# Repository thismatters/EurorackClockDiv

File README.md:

# Clock Divider (Binary)

This module reduces a clock signal by powers of two.

This is a hobbling together of elements featuring a three-layer stackup with a front face, a layer for all the jacks, and a power/processing layer where all the SMD components are layed out.

The input clock signal is passed through a schmitt trigger which is lifted whole-cloth from the [Yusynth Clock divider](https://yusynth.net/Modular/EN/DIVIDER/index.html) from which the reset signal processing is also lifted.
This module's function is distinct from the aforementioned Yusynth module in that it subdivides the clock by halves. The remainder of the circuit is a bog standard usage of the CD4040.

As with other modules in this line, this clock divider features:
* Polarity protection so that a backward power header doesn't fry anything (twin series schotty diodes: BAT54SL),
* Full surface mount design.

The KiCAD project here uses the library/footprints [found in my companion repo](https://github.com/thismatters/EurorackKiCAD).

## Width

11hp on an [Intellijel 1U rack](https://intellijel.com/support/1u-technical-specifications/).

## Inputs

Jacks:
* Input
* Reset

## Outputs

There are 6 output jacks each outputting a clock signal reduced by the labeled fraction.

## Adjustment

No adjustment required.

## Vendors

There are part numbers in the [BOM](clkdiv.csv) for many of the parts (not for basic passives though) at the following vendors:

* [Mouser](https://www.mouser.com): Needs no introduction. Get your ICs from here (or [digikey](https://www.digikey.com)).
* [Tayda Electronics](https://www.taydaelectronics.com/): Good supplier for passive components; audio jacks, and potentiometers. Their audio jacks are slightly smaller than the thonkiconn from thonk.
* [Love My Switches](https://lovemyswitches.com/): Has [really good knobs](https://lovemyswitches.com/anodized-aluminum-knob-the-lo-fi-1-4-smooth-shaft-12-5mm-od/) to go on those potentiometers!
* [OSHPark](https://oshpark.com/): Fast and (relatively) cheap PCB manufacturer. [V0 PCB](https://oshpark.com/shared_projects/ADWTtPJV)

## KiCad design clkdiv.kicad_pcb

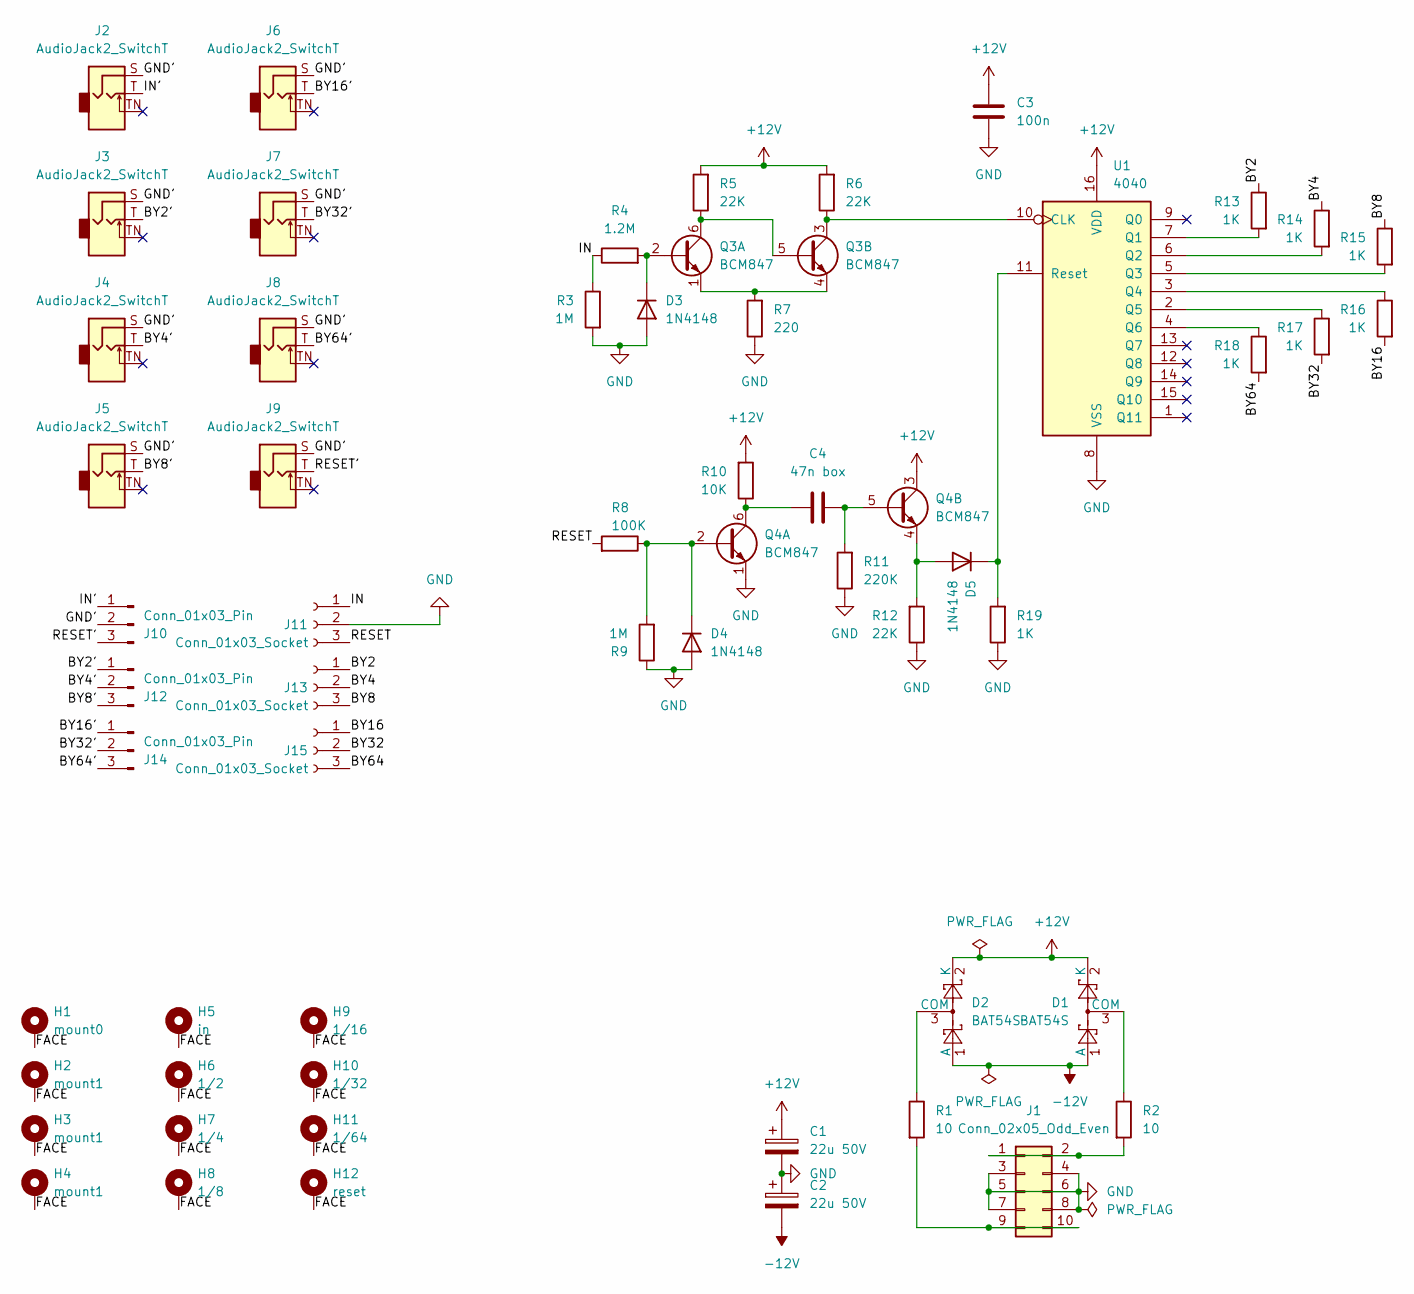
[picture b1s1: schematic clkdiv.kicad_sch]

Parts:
C1, C2: 22u 50V; CP_Radial_D5.0mm_P2.50mm
C3: 100n; C_0805_2012Metric
C4: 47n box; C_Rect_L7.2mm_W2.5mm_P5.00mm_FKS2_FKP2_MKS2_MKP2
D1, D2: BAT54S; SOT-23; PartNum 863-BAT54SLT1G
D3, D4, D5: 1N4148; D_SOD-323_HandSoldering
H1: mount0; Mech-MountingHole
H2, H3, H4: mount1; Mech-MountingHole
H5: in; Mech-AudioJack-Hole-Input-Clock
H6: 1/2; Mech-AudioJack-Hole-Output-Clock
H7: 1/4; Mech-AudioJack-Hole-Output-Clock
H8: 1/8; Mech-AudioJack-Hole-Output-Clock
H9: 1/16; Mech-AudioJack-Hole-Output-Clock
H10: 1/32; Mech-AudioJack-Hole-Output-Clock
H11: 1/64; Mech-AudioJack-Hole-Output-Clock
H12: reset; Mech-AudioJack-Hole-Input-Gate
J1: Conn_02x05_Odd_Even; PinHeader_2x05_P2.54mm_Vertical; PartNum A-2939
J2, J3, J4, J5, J6, J7, J8, J9: AudioJack2_SwitchT; AudioJack2_Tayda_A-2566; PartNum A-2566
J10, J12, J14: Conn_01x03_Pin; PinHeader_1x03_P2.54mm_Vertical
J11, J13, J15: Conn_01x03_Socket; PinSocket_1x03_P2.54mm_Vertical
Q3, Q4: BCM847; TSOP-6_1.65x3.05mm_P0.95mm; PartNum 771-BCM847DS135
R1, R2: 10; R_0805_2012Metric
R3, R9: 1M; R_0805_2012Metric
R4: 1.2M; R_0805_2012Metric
R5, R6, R12: 22K; R_0805_2012Metric
R7: 220; R_0805_2012Metric
R8: 100K; R_0805_2012Metric
R10: 10K; R_0805_2012Metric
R11: 220K; R_0805_2012Metric
R13, R14, R15, R16, R17, R18, R19: 1K; R_0805_2012Metric
U1: 4040; TSSOP-16_4.4x5mm_P0.65mm; PartNum 595-CD4040BPWR

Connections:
+12V: C1.1, C3.1, D1.2 (K), D2.2 (K), Q4.3 (C2), R5.2, R6.2, R10.2, U1.16 (VDD)
-12V: C2.2, D1.1 (A), D2.1 (A)
/BY2: J13.1, R13.1
/BY2': J3.T, J12.1
/BY4: J13.2, R14.1
/BY4': J4.T, J12.2
/BY8: J13.3, R15.1
/BY8': J5.T, J12.3
/BY16: J15.1, R16.2
/BY16': J6.T, J14.1
/BY32: J15.2, R17.2
/BY32': J7.T, J14.2
/BY64: J15.3, R18.2
/BY64': J8.T, J14.3
/FACE: H1.1, H2.1, H3.1, H4.1, H5.1, H6.1, H7.1, H8.1, H9.1, H10.1, H11.1, H12.1
/GND': J2.S, J3.S, J4.S, J5.S, J6.S, J7.S, J8.S, J9.S, J10.2
/IN: J11.1, R3.1, R4.1
/IN': J2.T, J10.1
/RESET: J11.3, R8.2
/RESET': J9.T, J10.3
GND: C1.2, C2.1, C3.2, D3.2 (A), D4.2 (A), J1.3, J1.4, J1.5, J1.6, J1.7, J1.8, J11.2, Q4.1 (E1), R3.2, R7.1, R9.1, R11.1, R12.1, R19.1, U1.8 (VSS)
unnamed: D1.3 (COM), R2.1
unnamed: D2.3 (COM), R1.1
unnamed: D3.1 (K), Q3.2 (B1), R4.2
unnamed: D4.1 (K), Q4.2 (B1), R8.1, R9.2
unnamed: D5.2 (A), Q4.4 (E2), R12.2
unnamed: D5.1 (K), R19.2, U1.11 (Reset)
unnamed: J1.1, J1.2, R2.2
unnamed: J1.9, J1.10, R1.2
unnamed: Q3.5 (B2), Q3.6 (C1), R5.1
unnamed: Q3.1 (E1), Q3.4 (E2), R7.2
unnamed: Q3.3 (C2), R6.1, U1.10 (CLK)
unnamed: C4.1, Q4.6 (C1), R10.1
unnamed: C4.2, Q4.5 (B2), R11.2
unnamed: R13.2, U1.7 (Q1)
unnamed: R14.2, U1.6 (Q2)
unnamed: R15.2, U1.5 (Q3)
unnamed: R16.1, U1.3 (Q4)
unnamed: R17.1, U1.2 (Q5)
unnamed: R18.1, U1.4 (Q6)

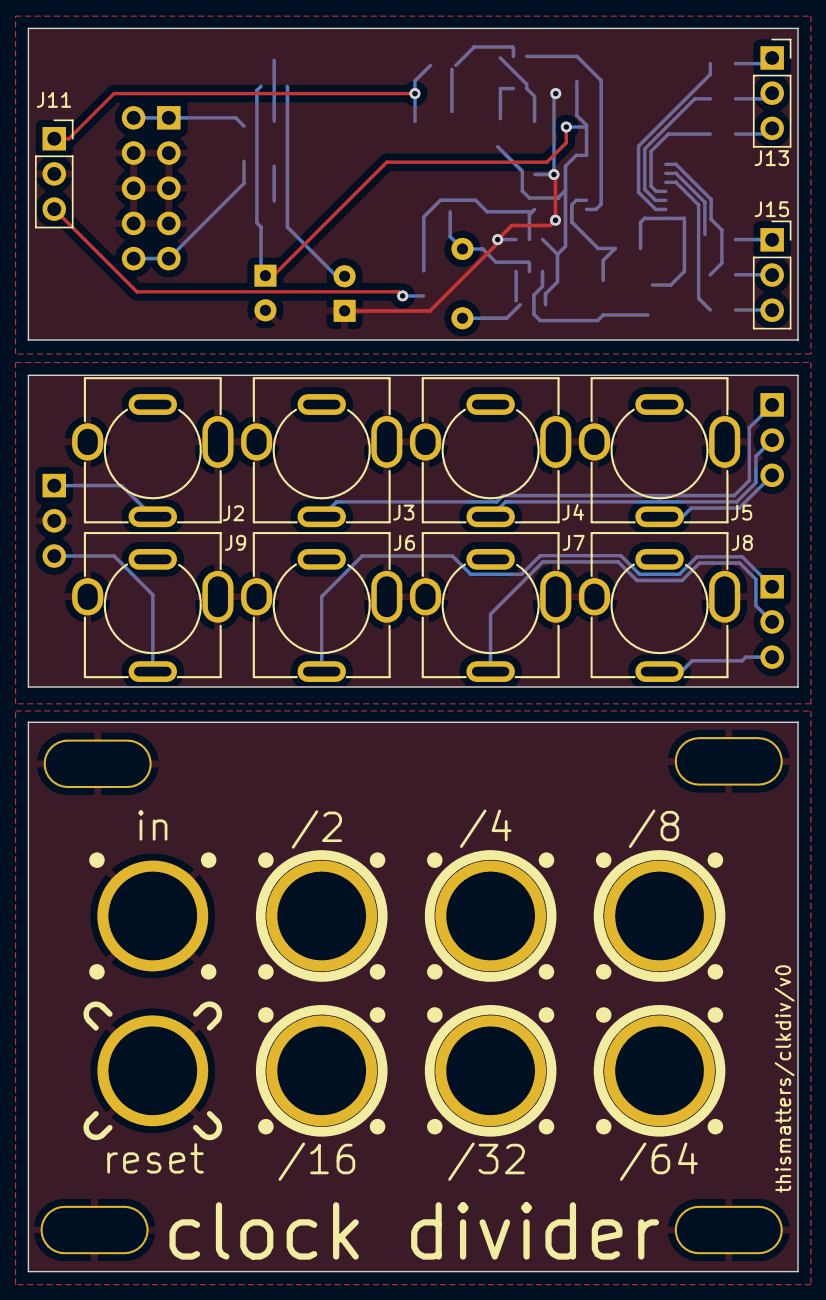
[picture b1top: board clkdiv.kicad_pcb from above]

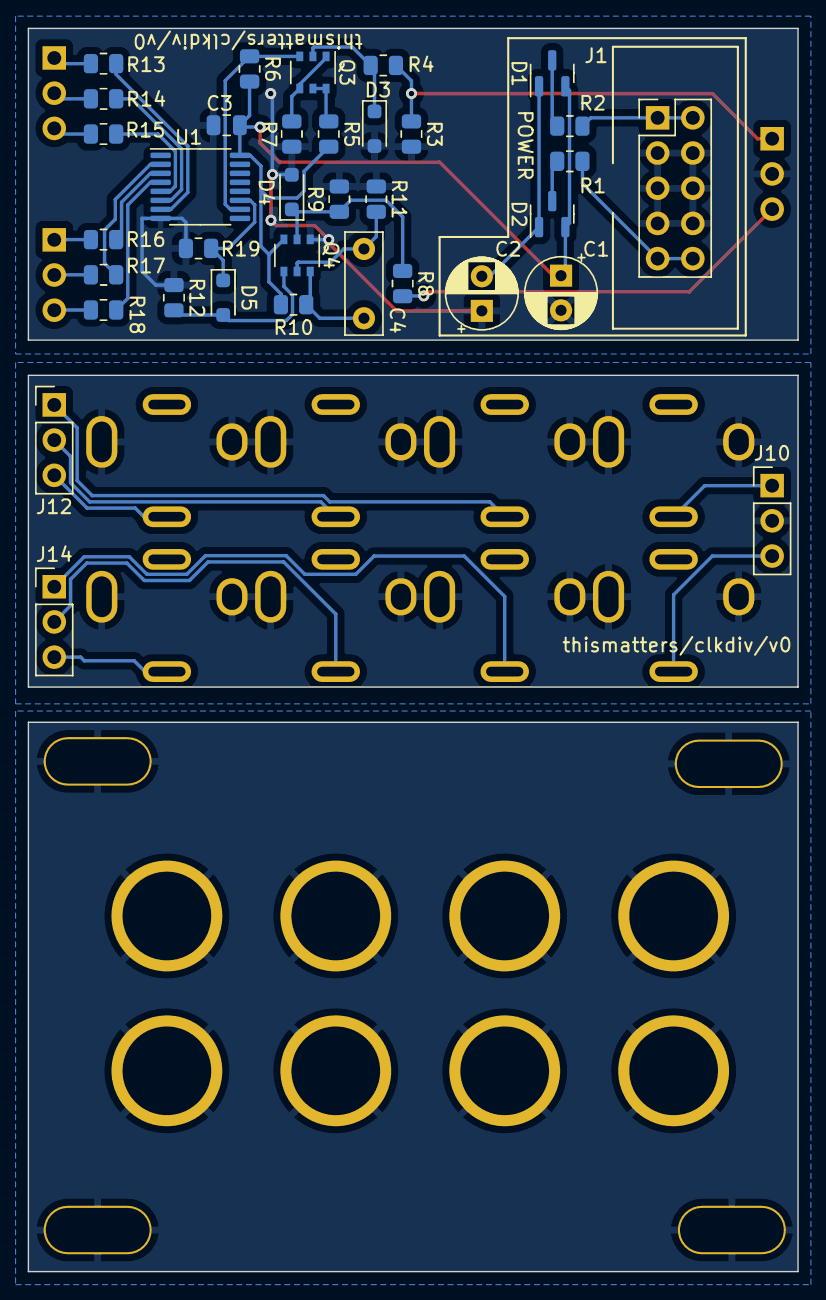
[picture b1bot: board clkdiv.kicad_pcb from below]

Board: 2 copper layers, 55.6 x 89.7 mm, 58 parts (35 on the bottom side), 40 nets.

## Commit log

2024-11-24 fixes after prototyping
2024-11-26 pcb laid out, bom generated
2024-12-06 readme changes
2025-01-11 publish PCB
